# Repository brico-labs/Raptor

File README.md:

# Raptor

This is the Raptor project repository

A followline robot with N20 motors, 16340 batteries, arduino pro micro and TB6612 or Raspberry Pi Zero.

This repository evolved
from [fstdp/openscad](https://github.com/fstdp/openscad), all openscad
files from the old repo are now on `openscad_misc`directory

# META

This repo
uses [BricoLabs KiCAD](https://github.com/brico-labs/bl_kicad_library)
Library as a submodule.

When cloning this repo you must:

~~~~{bash}
git clone https://github.com/brico-labs/Raptor
cd Raptor
git submodule init
git submodule update
~~~~

or just with one command:

~~~~{bash}
git clone --recursive https://github.com/brico-labs/Raptor
~~~~

# openscad_misc directory

variety of OpenSCAD things from different projects

- SpeedyGonZero, rearwing & ballcaster38 for Raspberry Pi Zero robot

# License MIT

Copyright 2017 Félix Sánchez-Tembleque

Permission is hereby granted, free of charge, to any person obtaining
a copy of this software and associated documentation files (the
"Software"), to deal in the Software without restriction, including
without limitation the rights to use, copy, modify, merge, publish,
distribute, sublicense, and/or sell copies of the Software, and to
permit persons to whom the Software is furnished to do so, subject to
the following conditions:

The above copyright notice and this permission notice shall be
included in all copies or substantial portions of the Software.

THE SOFTWARE IS PROVIDED "AS IS", WITHOUT WARRANTY OF ANY KIND,
EXPRESS OR IMPLIED, INCLUDING BUT NOT LIMITED TO THE WARRANTIES OF
MERCHANTABILITY, FITNESS FOR A PARTICULAR PURPOSE AND
NONINFRINGEMENT. IN NO EVENT SHALL THE AUTHORS OR COPYRIGHT HOLDERS BE
LIABLE FOR ANY CLAIM, DAMAGES OR OTHER LIABILITY, WHETHER IN AN ACTION
OF CONTRACT, TORT OR OTHERWISE, ARISING FROM, OUT OF OR IN CONNECTION
WITH THE SOFTWARE OR THE USE OR OTHER DEALINGS IN THE SOFTWARE.

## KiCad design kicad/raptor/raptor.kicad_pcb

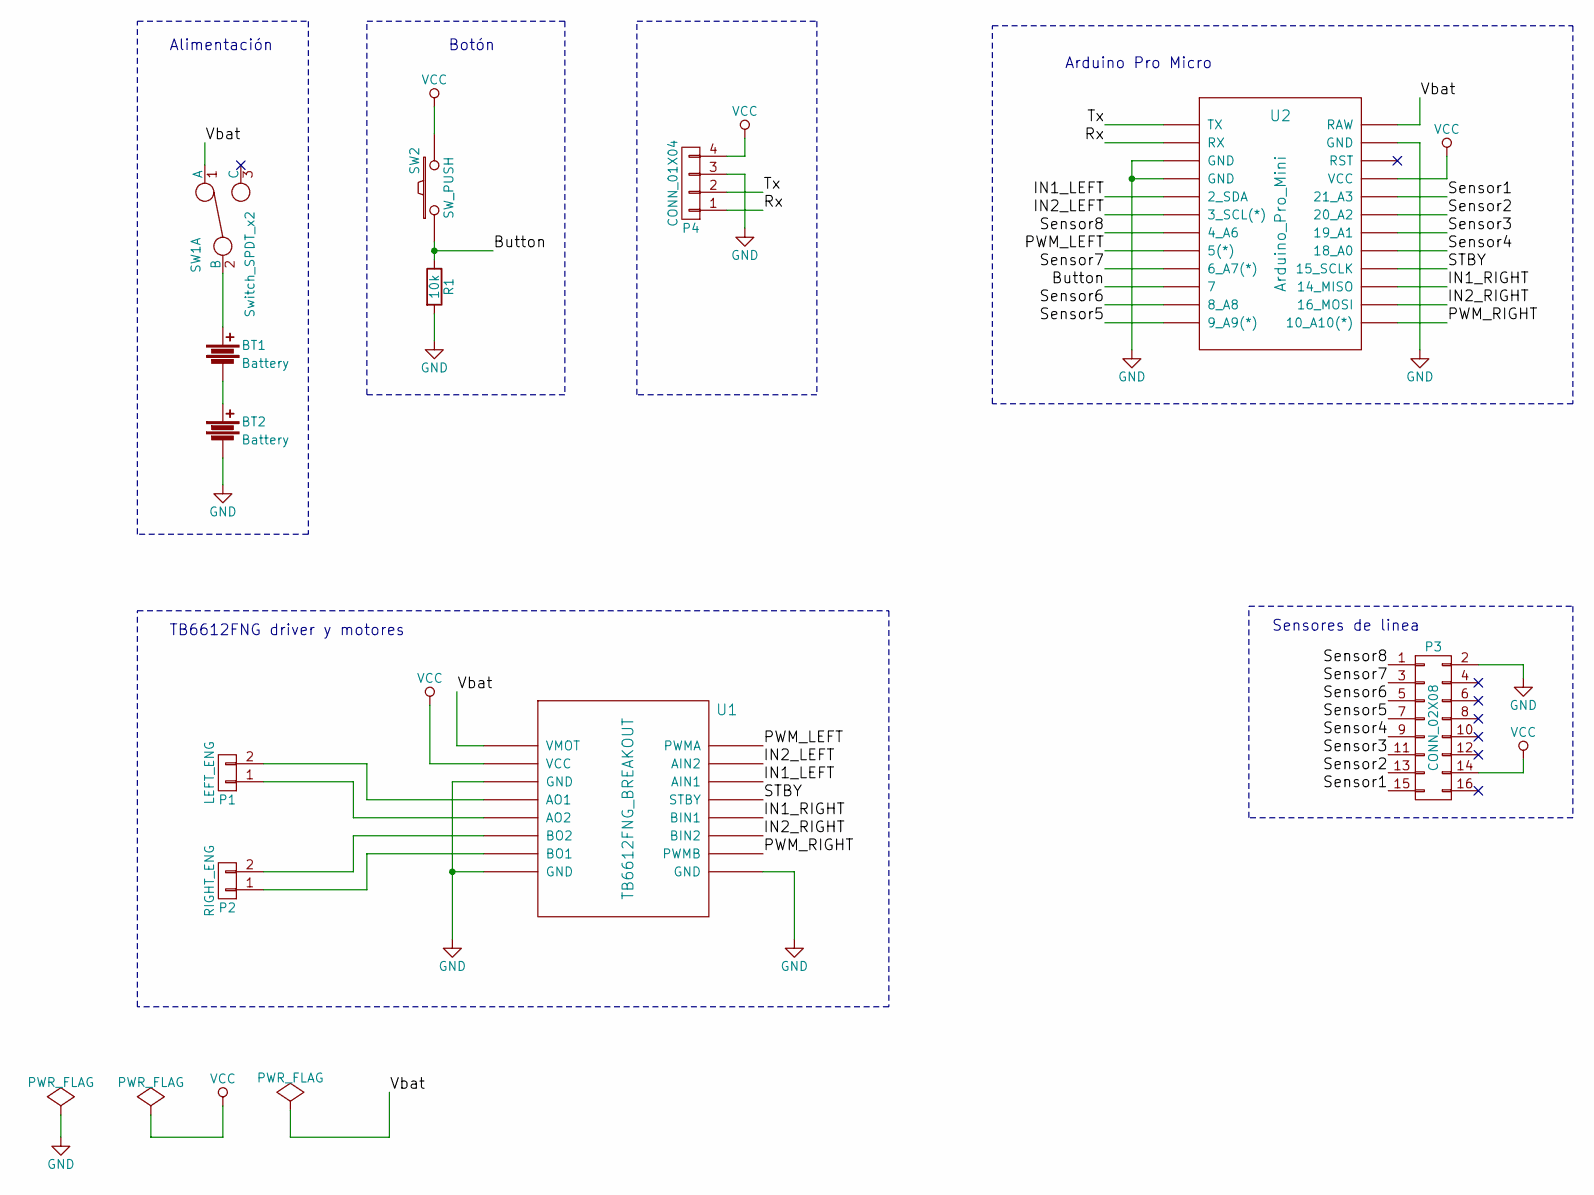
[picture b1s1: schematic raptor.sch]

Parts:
BT1, BT2: Battery; Battery_16340
P1: LEFT_ENG; Motor_raptor
P2: RIGHT_ENG; Motor_raptor
P3: CONN_02X08; Socket_Strip_Straight_2x08
P4: CONN_01X04; Socket_Strip_Straight_1x04
R1: 10k; Resistor_Horizontal_RM7mm
SW1: Switch_SPDT_x2; SW_Micro_SPST
SW2: SW_PUSH; SW_PUSH-12mm
U1: TB6612FNG_BREAKOUT; DIP-16_600
U2: Arduino_Pro_Mini; DIP-24_600

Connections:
/Button: R1.1, SW2.1, U2.10 (7)
/IN1_LEFT: U1.14 (AIN1), U2.5 (2_SDA)
/IN1_RIGHT: U1.12 (BIN1), U2.15 (14_MISO)
/IN2_LEFT: U1.15 (AIN2), U2.6 (3_SCL(*))
/IN2_RIGHT: U1.11 (BIN2), U2.14 (16_MOSI)
/PWM_LEFT: U1.16 (PWMA), U2.8 (5(*))
/PWM_RIGHT: U1.10 (PWMB), U2.13 (10_A10(*))
/Rx: P4.1, U2.2 (RX)
/STBY: U1.13 (STBY), U2.16 (15_SCLK)
/Sensor1: P3.15, U2.20 (21_A3)
/Sensor2: P3.13, U2.19 (20_A2)
/Sensor3: P3.11, U2.18 (19_A1)
/Sensor4: P3.9, U2.17 (18_A0)
/Sensor5: P3.7, U2.12 (9_A9(*))
/Sensor6: P3.5, U2.11 (8_A8)
/Sensor7: P3.3, U2.9 (6_A7(*))
/Sensor8: P3.1, U2.7 (4_A6)
/Tx: P4.2, U2.1 (TX)
/Vbat: SW1.1 (A), U1.1 (VMOT), U2.24 (RAW)
GND: BT2.2, P3.2, P4.3, R1.2, U1.3 (GND), U1.8 (GND), U1.9 (GND), U2.3 (GND), U2.4 (GND), U2.23 (GND)
unnamed: BT1.1, SW1.2 (B)
unnamed: BT1.2, BT2.1
unnamed: P1.1, U1.5 (AO2)
unnamed: P1.2, U1.4 (AO1)
unnamed: P2.1, U1.7 (BO1)
unnamed: P2.2, U1.6 (BO2)
VCC: P3.14, P4.4, SW2.2, U1.2 (VCC), U2.21 (VCC)

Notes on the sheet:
Alimentación
Botón
TB6612FNG driver y motores
Sensores de linea
Arduino Pro Micro

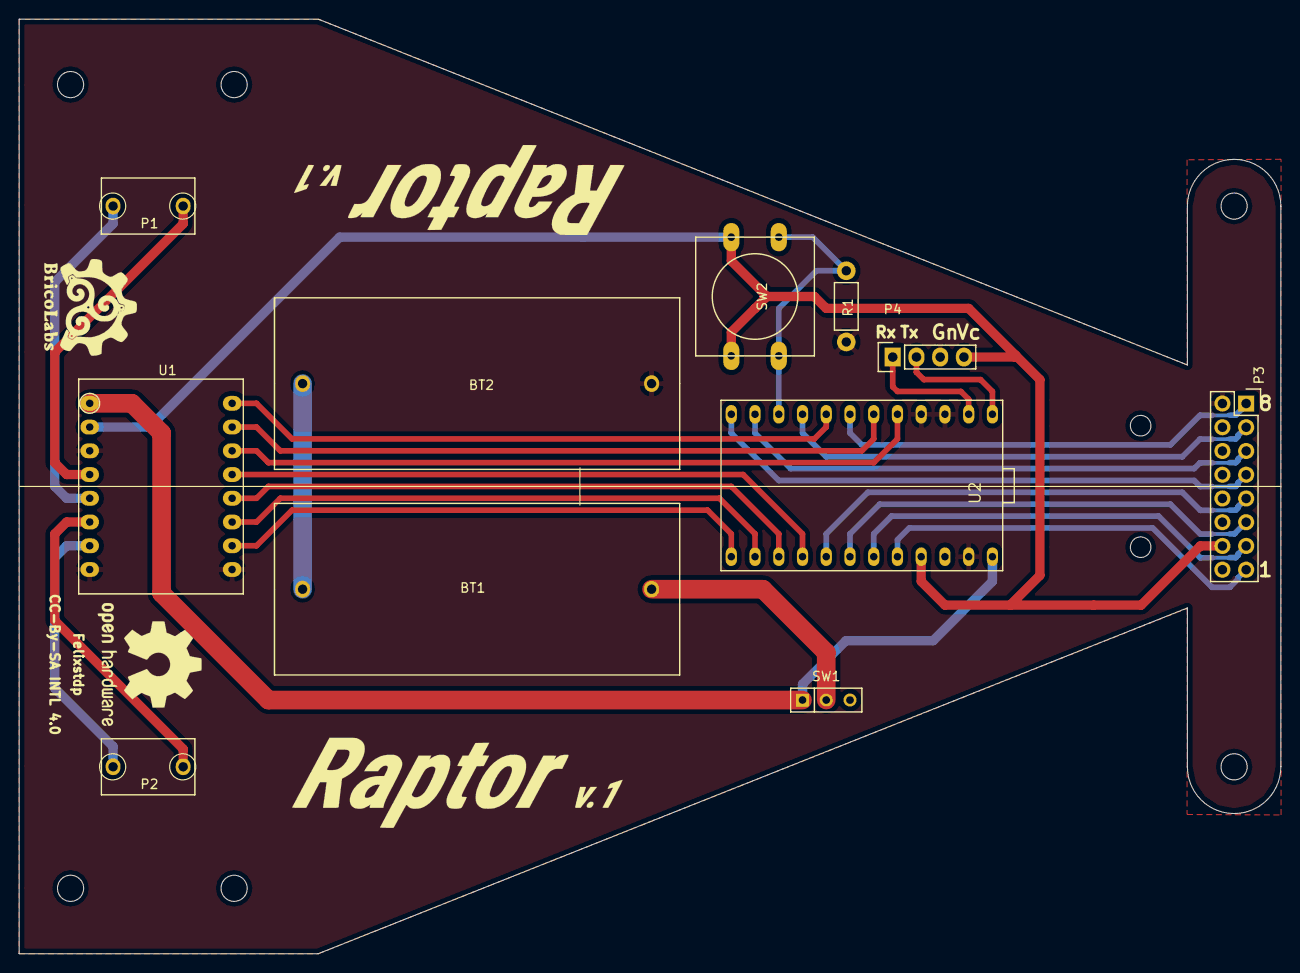
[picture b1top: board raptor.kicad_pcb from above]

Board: 2 copper layers, 135.0 x 100.0 mm, 11 parts (0 on the bottom side), 27 nets.

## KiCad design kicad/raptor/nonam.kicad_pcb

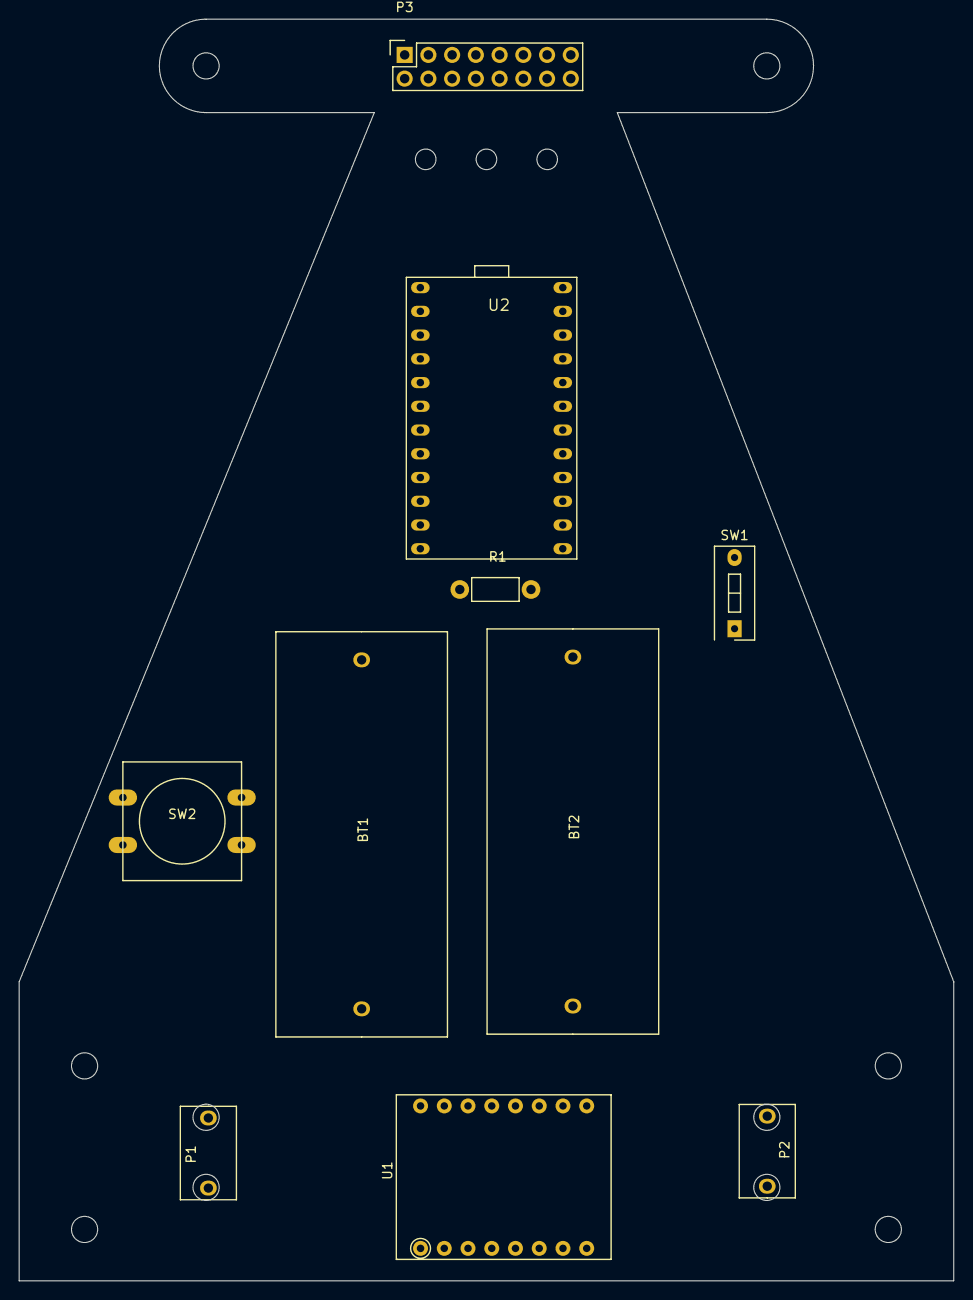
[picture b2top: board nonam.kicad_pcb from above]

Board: 2 copper layers, 100.0 x 135.0 mm, 10 parts (0 on the bottom side), 24 nets, no tracks yet.

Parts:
BT1, BT2: Battery; Battery_16340
P1: LEFT_ENG; Motor_raptor
P2: RIGHT_ENG; Motor_raptor
P3: CONN_02X08; Socket_Strip_Straight_2x08
R1: 10k; Resistor_Horizontal_RM7mm
SW1: SPST; SW_DIP_x1_Slide
SW2: SW_PUSH; SW_PUSH-12mm
U1: TB6612FNG_BREAKOUT; DIP-16_600
U2: Arduino_Pro_Mini; DIP-24_600

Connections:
/Button: R1.1, SW2.1, U2.10
/IN1_LEFT: U1.14, U2.5
/IN1_RIGHT: U1.12, U2.15
/IN2_LEFT: U1.15, U2.6
/IN2_RIGHT: U1.11, U2.14
/PWM_LEFT: U1.16, U2.8
/PWM_RIGHT: U1.10, U2.13
/STBY: U1.13, U2.16
/Sensor1: P3.16, U2.17
/Sensor2: P3.14, U2.18
/Sensor3: P3.12, U2.19
/Sensor4: P3.10, U2.20
/Sensor5: P3.8, U2.7
/Sensor6: P3.6, U2.9
/Sensor7: P3.4, U2.11
/Sensor8: P3.2, U2.12
GND: BT2.2, P3.1, R1.2, U1.1, U1.8, U1.9, U2.3, U2.4, U2.23
unnamed: BT1.1, SW1.1
unnamed: BT1.2, BT2.1
unnamed: P1.1, U1.4
unnamed: P1.2, U1.3
unnamed: P2.1, U1.6
unnamed: P2.2, U1.5
VCC: P3.13, SW1.2, SW2.2, U1.2, U2.24

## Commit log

2017-04-04 Root directory renamed Cleaning up root directory Created doc directory
2017-04-04 Added BricoLabs KiCAD library as submodule on Raptor KiCAD project
2017-04-05 Added instructions for BricoLabs Library submodule use
2017-04-05 Added dxf LibreCAD file for Raptor PCB
2017-09-24 Some cleaning
2018-02-04 Update README.md
    Cloning repos with submodules.

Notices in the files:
kicad/raptor/raptor.kicad_pcb:
CC-By-SA-INTL 4.0
